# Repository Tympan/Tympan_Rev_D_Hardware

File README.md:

# Tympan Rev D Hardware
Repository for Tympan Rev D electronics and case designs

## Features

* Based on Teensy 3.6
* TLV320AIC3206 CODEC
* On board MEMS Microphone SPM0687LR5H-1
* BC127 Bluetooth module with audio support
* LiPo Battery Charge Circuit
* CODEC Line In/Out breakout
* UART breakout
* I2C breakout
* SPI breakout
* I2S breakout
* Teensy RTC battery breakout

### Tympan Rev D breakout pins compatible with Tympan AIC Codec Shield. Add 2 more channels to your Tympan!

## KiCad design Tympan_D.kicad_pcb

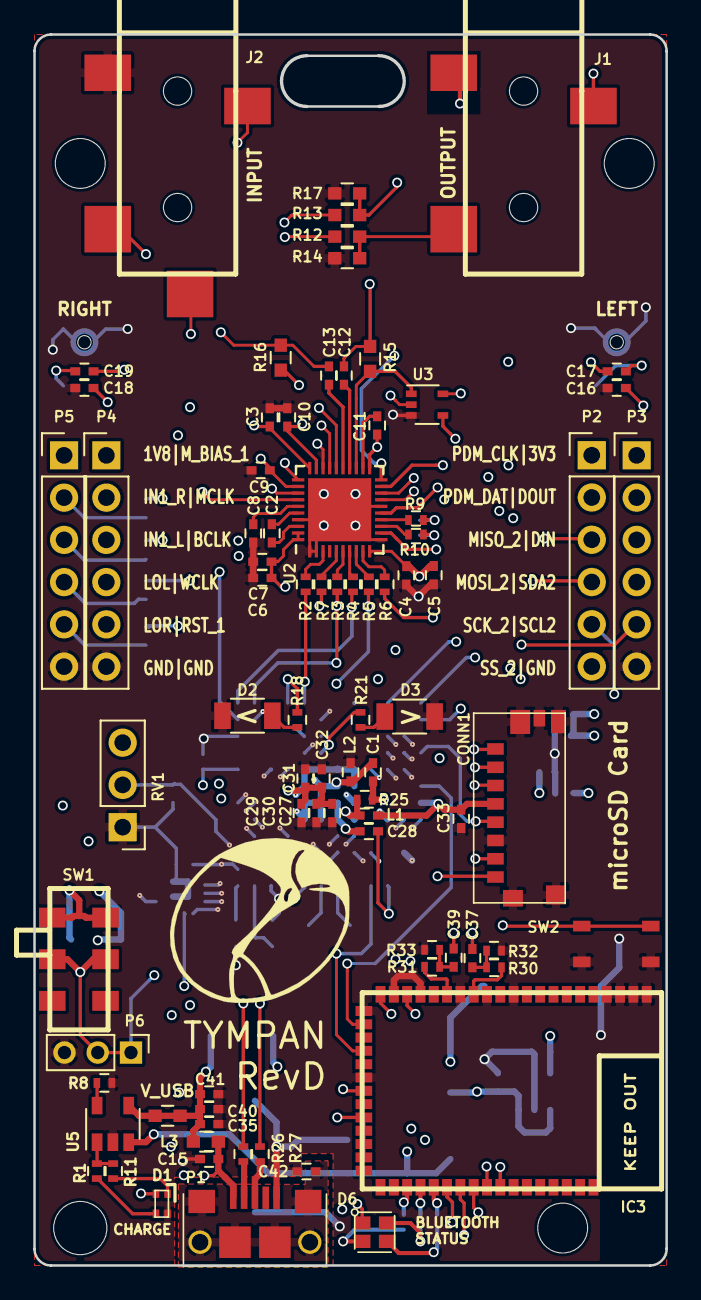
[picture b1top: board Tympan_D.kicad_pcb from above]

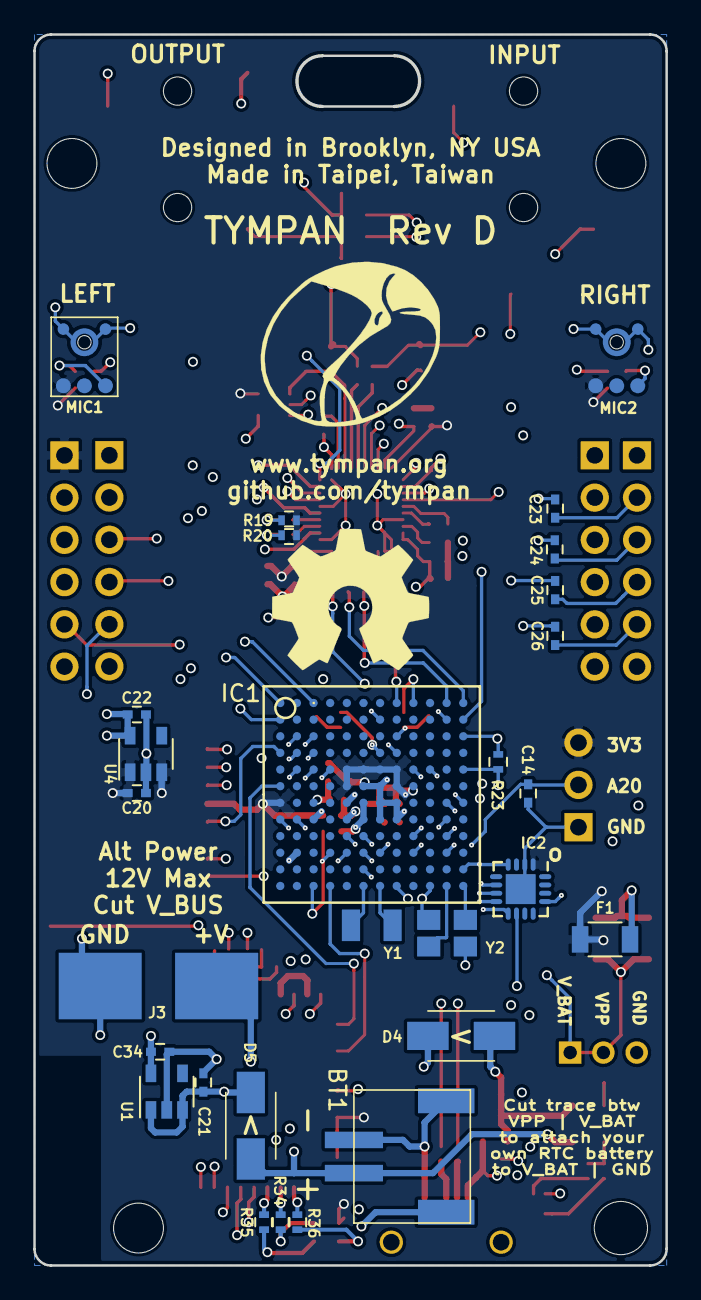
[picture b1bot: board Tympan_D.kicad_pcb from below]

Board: 4 copper layers, 38.0 x 74.0 mm, 113 parts (28 on the bottom side), 117 nets.

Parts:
BT1: 4UCON-20519; 4UCON-0217-20519
C1, C3, C5, C7, C10, C14, C16, C18, C28, C29, C42: 0.1uF; C_0402
C2, C8, C12, C13, C23, C24, C25, C26, C27, C32, C33, C37, C39: 2.2uF; C_0402
C4, C6, C11, C15: 10uF; C_0402
C9, C17, C19, C20, C21, C22, C34: 1uF; C_0402
C30, C31: 10nF; C_0402
C35: 4.7uF; C_0402
C40: 15pF; C_0402
C41: 22nF; C_0402
CONN1: 8_PIN_microSD; MOLEX_47571-0001
D1: APHB1608SGNC; ABHB1608S
D2, D3: LED; C_1206
D4, D5: Shottkey; ACDBA340-HF
D6: Led_RGB_CA; CLMVB-FKA-CFHEHLCBB7a363
F1: FUSE; C_1206
IC1: MK66FX1M0VMD18; BGA-144-1mm
IC2: MKL02Z32VFG4; QFN-16-1EP_3x3mm_Pitch0.5mm
IC3: BC127
J1: SJ-3523-SMT-TR
J2: SJ-3524-SMT-TR-PI; SJ-3524-SMT-TR
J3: alt Power Pads
L1, L2: 600R; C_0402
L3: 1K; C_0603
MIC1, MIC2: SPM0687LR5H-1
P1: USB_OTG; 10118193_microUSB
P2, P3, P4, P5: CONN_01X06; Pin_Header_Straight_1x06_Pitch2.54mm
P6: CONN_01X03; Pin_Header_Straight_1x03_Pitch2.00mm
P7: CONN_01X01; NPTH_2.4mm
P8, P9, P10: CONN_01X01; NPTH_3.2mm
R1, R11, R19, R20, R32, R33: 1K; R_0402
R2, R3, R4, R5, R6, R7, R9, R10, R26, R27: 33R; R_0402
R8: 2.2K; R_0402
R12, R13: 0R; C_0603
R14, R17: DNP; C_0603
R15, R16: 2.2K; C_0603
R18, R21, R34, R35, R36: 240R; R_0402
R23: 100K; R_0402
R25: 470R; R_0402
R30, R31: 10K; R_0402
RV1: POT; Pin_Header_Straight_1x03_Pitch2.54mm
SW1: CL-SB-22A
SW2: TACT_SWITCH; PTS810
U1: AP2210K-3.3TRG1; SOT-23-5
U2: TLV320AIC3206IRSBT; UQFN-40-1EP_5x5mm_Pitch0.4mm
U3: 74LVC1G66; SOT-353_SC-70-5
U4: LP5907MFX-1.8; SOT-23-5
U5: MCP73831; SOT-23-5
V_USB: DNP; C_0603
Y1: 32.768kHz; LFXTAL009678
Y2: 16MHz; FA_238_16.0000MB_K3

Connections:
+1V8: C6.1, C7.1, C9.1, C10.1, C22.1, P5.1, U2.29, U2.32, U2.39, U2.40, U4.5
+3V3: C3.2, C4.2, C5.2, C16.2, C18.2, C20.1, C27.1, C29.1, C30.1, C31.1, C32.1, C33.1, CONN1.4, D6.1, F1.2, IC1.E5, IC1.E6, IC1.E7, IC1.E8, IC1.F5, IC1.F8, IC1.G1, IC2.1, IC3.30, IC3.31, IC3.32, IC3.33, L1.2, MIC1.4, MIC2.4, P3.1, R19.1, R20.1, RV1.3, U2.10, U2.30, U3.5, U4.1, U4.3
+BATT: BT1.1, D5.2, J3.1, U5.3
/BCLK: IC1.A11, P4.3, R3.1
/BT_CTS: IC1.M8, IC3.40
/BT_PIO0: IC1.F1, IC3.23
/BT_PIO5: IC1.M4, IC3.25
/BT_RTS: IC1.K4, IC3.43
/BT_RX: IC1.E9, IC3.42
/BT_TX: IC1.E10, IC3.41
/BT_nRESET: IC1.K5, IC3.44
/CLK: CONN1.5, IC1.D1
/CMD: CONN1.3, IC1.E4
/DAT0: CONN1.7, IC1.D2
/DAT1: CONN1.8, IC1.D3
/DAT2: CONN1.1, IC1.E2
/DAT3: CONN1.2, IC1.E3
/DIN: IC1.B11, R5.1
/DIN_1: IC1.B12, P3.3
/DOUT: IC1.D8, R6.1
/DOUT_1: IC1.B7, P3.2
/HPL: R12.1, U2.31
/HPR: R13.1, U2.33
/IN1_L: C24.1, C37.1, U2.17
/IN1_R: C23.1, C39.1, U2.18
/IN2_L: C17.1, U2.19
/IN2_R: C19.1, U2.20
/LED_0: IC3.37, R36.1
/LED_1: IC3.38, R34.1
/LED_2: IC3.39, R35.1
/LOL: C25.1, IC3.21, U2.26
/LOR: C26.1, IC3.19, U2.27
/MCLK: IC1.C8, P4.2, R7.1
/MICBIAS: R15.1, U2.23, U3.1
/MICDET: J2.4, U2.34
/MISO_2: IC1.C2, P2.3
/MOSI_2: IC1.C3, P2.4
/M_BIAS: IC1.A3, U3.4
/M_BIAS_1: IC1.H11, P4.1
/PDM_CLK: P2.2, U2.12
/PDM_DAT: P2.1, U2.15
/POT: C14.1, IC1.K11, RV1.2
/PROG: IC2.10, SW2.1, SW2.2
/PTA0: IC1.J5, IC2.8
/PTA1: IC1.J6, IC2.6
/PTA2: IC1.K6, IC2.9
/PTA3: IC1.K7, IC2.7
/RESET_B: IC1.L12, IC2.4, IC2.13
/SCK_2: IC1.B1, P2.5
/SCL2: IC1.K9, P3.5
/SCL/SS: IC1.G12, R10.1, R20.2
/SDA2: IC1.J9, P3.4
/SDA/MOSI: IC1.G11, R9.1, R19.2
/SS_2: IC1.A1, P2.6
/USB: C15.1, D1.3, L3.1, P1.1
/USB0_D+: IC1.H1, R27.2
/USB0_D-: IC1.H2, R26.2
/VREGEN: IC1.E12, IC3.28, R23.1
/V_USB: C35.1, C40.1, C41.1, D4.2, L3.2, U5.4, V_USB.1, V_USB.2
/WCLK: IC1.A12, P4.4, R4.1
/nRESET: IC1.A8, R2.1
/nRESET_1: IC1.J11, P4.5
Earth: C42.2, P1.6, P1.7, P1.8, P1.9, P1.10, P1.11
GND: BT1.2, BT1.3, BT1.4, C3.1, C4.1, C5.1, C6.2, C7.2, C8.2, C9.2, C10.2, C11.2, C14.2, C15.2, C16.1, C18.1, C20.2, C21.2, C22.2, C27.2, C29.2, C30.2, C31.2, C32.2, C33.2, C34.2, C35.2, C40.2, C41.2, C42.1, CONN1.6, CONN1.9, CONN1.10, CONN1.11, CONN1.12, CONN1.13, D1.2, D2.1, D3.1, IC1.C12, IC1.F6, IC1.F7, IC1.G7, IC1.G8, IC1.H3, IC1.H7, IC1.H8, IC1.K2, IC1.M10, IC2.2, IC2.17, IC3.1, IC3.2, IC3.3, IC3.4, IC3.11, IC3.13, IC3.15, IC3.18, IC3.20, IC3.22, IC3.27, J1.1, J2.1, J3.2, L2.2, MIC1.2, MIC1.3, MIC2.2, MIC2.3, P1.5, P3.6, P4.6, P5.6, P6.3, R8.2, R14.2, R17.2, R23.2, R32.2, R33.2, RV1.1, SW2.3, SW2.4, U1.2, U2.1, U2.2, U2.11, U2.16, U2.21, U2.28, U2.37, U2.41, U3.3, U4.2, U5.2, Y2.2, Y2.4
unnamed: C1.1, C28.1, IC1.G6, IC1.H6, L2.1
unnamed: C1.2, IC1.G5, R25.1
unnamed: C2.1, U2.36
unnamed: C2.2, U2.38
unnamed: C8.1, U2.35
unnamed: C11.1, U2.22
unnamed: C12.1, U2.24
unnamed: C12.2, J2.2, R15.2
unnamed: C13.1, U2.25
unnamed: C13.2, J2.3, R16.1
unnamed: C17.2, MIC1.1
unnamed: C19.2, MIC2.1
unnamed: C21.1, D4.1, D5.1, U1.1, U1.3
unnamed: C23.2, P5.2
unnamed: C24.2, P5.3
unnamed: C25.2, P5.4
unnamed: C26.2, P5.5
unnamed: C28.2, IC1.M3
unnamed: C37.2, R30.2, R32.1
unnamed: C39.2, R31.2, R33.1
unnamed: D1.1, R11.1
unnamed: D1.4, R1.1
unnamed: D2.2, R18.2
unnamed: D3.2, R21.2
unnamed: D6.2, R34.2
unnamed: D6.3, R35.2
unnamed: D6.4, R36.2
unnamed: F1.1, SW1.1, SW1.4
unnamed: IC1.A9, R18.1
unnamed: IC1.D7, R21.1
unnamed: IC1.H5, L1.1, R25.2
unnamed: IC1.M6, Y1.1
unnamed: IC1.M7, Y1.2
unnamed: IC1.M11, Y2.1
unnamed: IC1.M12, Y2.3
unnamed: IC3.14, R30.1
unnamed: IC3.16, R31.1
unnamed: J1.2, R12.2, R14.1
unnamed: J1.3, R13.2, R17.1
unnamed: P1.2, R26.1
unnamed: P1.3, R27.1
unnamed: R1.2, R11.2, U5.1
unnamed: R2.2, U2.3
unnamed: R3.2, U2.6
unnamed: R4.2, U2.7
unnamed: R5.2, U2.8
unnamed: R6.2, U2.9
unnamed: R7.2, U2.5
unnamed: R8.1, U5.5
unnamed: R9.2, U2.14
unnamed: R10.2, U2.13
unnamed: R16.2, U3.2
VPP: C34.1, IC1.L6, P6.1, P6.2, SW1.2, SW1.5, U1.5

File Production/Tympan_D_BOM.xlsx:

Item | Reference | Package | Quantity | Value | Manufacturer | Part Number | Notes
1 | BT1 | 4UCON-0217-20519 | 1 | 4UCON-20519 | 4UCON | 20519 | Consigned by Solutions
2 | C1,C3,C5,C7,C10,C14,C16,C18,C28,C29,C42 | C_0402 | 11 | 0.1uF | TDK Corporation | C1005X7R1H104K050BB
3 | C2,C8,C12,C13,C23,C24,C25,C26,C27,C32,C33,C37,C39 | C_0402 | 13 | 2.2uF | Murata | GRT155C71A225KE13D
4 | C30,C31 | C_0402 | 2 | 10nF | Yageo | AC0402KPX7R9BB103
5 | C35 | C_0402 | 1 | 4.7uF | TDK Corporation | C1005X5R1A475K050BC
6 | C4,C6,C11,C15 | C_0402 | 4 | 10uF | Murata | GRM155C80J106ME11J
7 | C40 | C_0402 | 1 | 15pF | Wurth | 885012005008
8 | C41 | C_0402 | 1 | 22nF | Wurth | 885012205014
9 | C9,C17,C19,C20,C21,C22,C34 | C_0402 | 7 | 1uF | Murata | GRM155C81C105KE15D
10 | CONN1 | MOLEX_47571-0001 | 1 | 8_PIN_microSD | Molex | 47571-0001
11 | D1 | ABHB1608S | 1 | 2 color LED | Everlight | 18-225SURSYGC/S530-A4/E4/TR8
12 | D2 | C_1206 | 1 | LED Red | Lite-On | LTST-C150EKT
13 | D3 | C_1206 | 1 | LED Amber | Lite-On | LTST-C150AKT
14 | D4,D5 | ACDBA340-HF | 2 | Shottkey | Comchip | ACDBA340-HF
15 | D6 | CLMVB-FKA-CFHEHLCBB7a363 | 1 | Led_RGB_CA | Cree | CLMVB-FKA-CFHEHLCBB7a363
16 | F1 | C_1206 | 1 | FUSE | Bell Fuse | C1Q 1
17 | IC1 | BGA-144-1mm | 1 | ARM | NXP | MK66FX1M0VMD18
18 | IC2 | QFN-16-1EP_3x3mm_Pitch0.5mm | 1 | MKL02Z32VFG4 | PJRC | IC_MKL02Z32_QFN16 | Consigned by Solutions
19 | IC3 | BC127 | 1 | BC127 | Sierra Wireless | BC127-1103383
20 | J1 | SJ-3523-SMT-TR | 1 | Phone Out | CUI Inc | SJ-3523-SMT-TR
21 | J2 | SJ-3524-SMT-TR | 1 | Mic In | CUI Inc | SJ-3524-SMT-TR-PI
22 | L1,L2 | C_0402 | 2 | 600R | TDK Corporation | MMZ1005S601HT000
23 | L3 | C_0603 | 1 | 1K | Murata | BLM18KG102SH1D
24 | MIC2,MIC1 | SPM0687LR5H-1 | 2 | MEMS Microphone | Knowles | SPM0687LR5H-1
25 | P1 | 10118193_microUSB | 1 | USB_OTG | Amphenol | 10118193-0001LF
26 | P3,P4,P5,P2 | Pin_Header_Straight_1x06_Pitch2.54mm | 4 | CONN_01X06 | Samtec | SSW-106-01-G-S
27 | P6 | Pin_Header_Straight_1x03_Pitch2.00mm | 1 | DNP | DNP | DNP | DNP
28 | R12,R13 | C_0603 | 2 | 0R | Vishay Dale | CRCW06030000Z0EA
29 | R14,R17 | C_0603 | 2 | DNP | DNP | DNP | DNP
30 | R15,R16 | C_0603 | 2 | 2.2K | Yageo | RC0603FR-072K2L
31 | R18,R21 | R_0402 | 2 | 240R | Yageo | RC0402JR-07240RL
32 | R19,R20,R32,R33,R1,R11 | R_0402 | 6 | 1K | Vishay Dale | CRCW04021K00FKED
33 | R23 | R_0402 | 1 | 100K | Vishay Dale | CRCW0402100KFKED
34 | R25,R34,R35,R36 | R_0402 | 4 | 470R | Yageo | RC0402FR-07470RL
35 | R30,R31 | R_0402 | 2 | 10K | Yageo | RC0402FR-0710KL
36 | R6,R2,R3,R4,R5,R7,R9,R10,R26,R27 | R_0402 | 10 | 33R | Yageo | RC0402FR-0733RL
37 | R8 | R_0402 | 1 | 2.2K | Yageo | RC0402JR-0722KL
38 | RV1 | Pin_Header_Straight_1x03_Pitch2.54mm | 1 | POT | Bourns | 3352T-1-103L
39 | SW1 | CL-SB-22A | 1 | Slide Switch | Nidec Copal | CL-SB-22A-11T
40 | SW2 | PTS810 | 1 | TACT_SWITCH | C&K | PTS810 SJK 250 SMTR LFS
41 | U1 | SOT-23-5 | 1 | 3V3 Regulator | Diodes Inc | AP2210K-3.3TRG1
42 | U2 | UQFN-40-1EP_5x5mm_Pitch0.4mm | 1 | CODEC | Texas Instrument | TLV320AIC3206IRSBT
43 | U3 | SOT-353_SC-70-5 | 1 | Analog Switch IC | Texas Instrument | TS5A3166DCKR
44 | U4 | SOT-23-5 | 1 | 1V8 Regulator | Texas Instrument | LP5907MFX-1.8/NOPB
45 | U5 | SOT-23-5 | 1 | LiPo Charge IC | Microchip | MCP73831T-2DCI/OT
46 | Y1 | LFXTAL009678 | 1 | 32.768kHz | IQD | LFXTAL009678Reel
47 | Y2 | FA_238_16.0000MB_K3 | 1 | 16MHz | Epson | FA_238_16.0000MB_K3

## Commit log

2018-05-30 Added STEP files
2018-05-30 Renamed files for consistency
2019-01-12 Updated with latest version of the hardware
2019-03-01 Adjusted tracks. Switched PIO0
    Moved PIO0 to a digital pin
    Moved tracks from under the xtal per PJRC
    Cleaned up speaker out ground trace
2019-03-06 Updated changes from client
2019-03-06 Update to readme
2019-03-06 updated schematic pdf
2019-03-15 Update sym-lib-table
2019-03-15 fixed broken symbols
2019-03-16 Final changes to PCB
2019-03-16 Moved breadout schematics for clarity
2019-03-18 Made Production Files
2019-03-19 updated schematics
2019-03-26 added some more dimensions
2019-04-02 tightened solder mask around pads per CM recommendation
2019-04-15 Renamed schematic PDF
2019-04-15 edits
2019-04-15 quickest way to do this
2020-01-31 renamed files that were braking windows
2020-01-31 Added CAD for PCB ASSY
    Added CAD as assembly, single part (exterior faces), or STEP
2020-02-06 finally added current production STL files
2020-04-03 added some of the 3d files to the model for rendering and export
2020-12-10 switched '+ -' label for battery connect to correct it
2020-12-10 Noted Jack Mistake on schematics & updated pdf
2021-01-23 Changed the PDM pins
    Also added Melody User Guides for reference
2021-01-23 Updated Schematic PDF with note about PDM pin swap
2021-06-07 added licensing for the documentation as per the OSHWA Certification
